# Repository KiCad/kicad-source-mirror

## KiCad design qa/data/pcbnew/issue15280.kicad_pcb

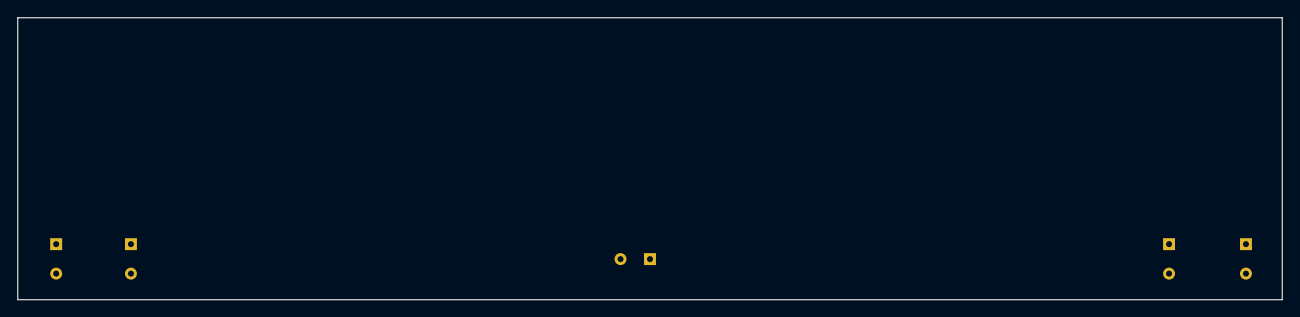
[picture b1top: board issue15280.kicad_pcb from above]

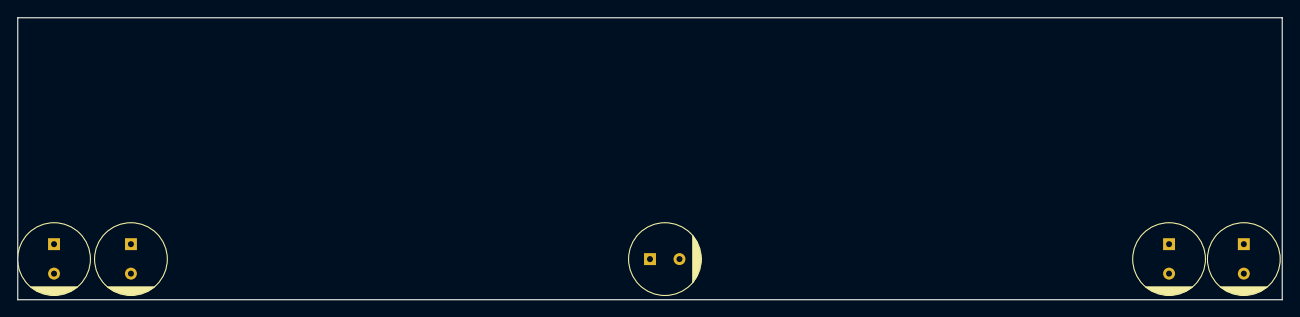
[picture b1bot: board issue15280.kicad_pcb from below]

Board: 8 copper layers, 148.0 x 33.0 mm, 5 parts (5 on the bottom side), 2 nets, no tracks yet.

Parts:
C101, C102, C311, C511, C708: 22u; CP_Rad_D8_H6

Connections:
/Motor1/VMOT: C101.1, C102.1, C311.1, C511.1, C708.1
GND: C101.2, C102.2, C311.2, C511.2, C708.2

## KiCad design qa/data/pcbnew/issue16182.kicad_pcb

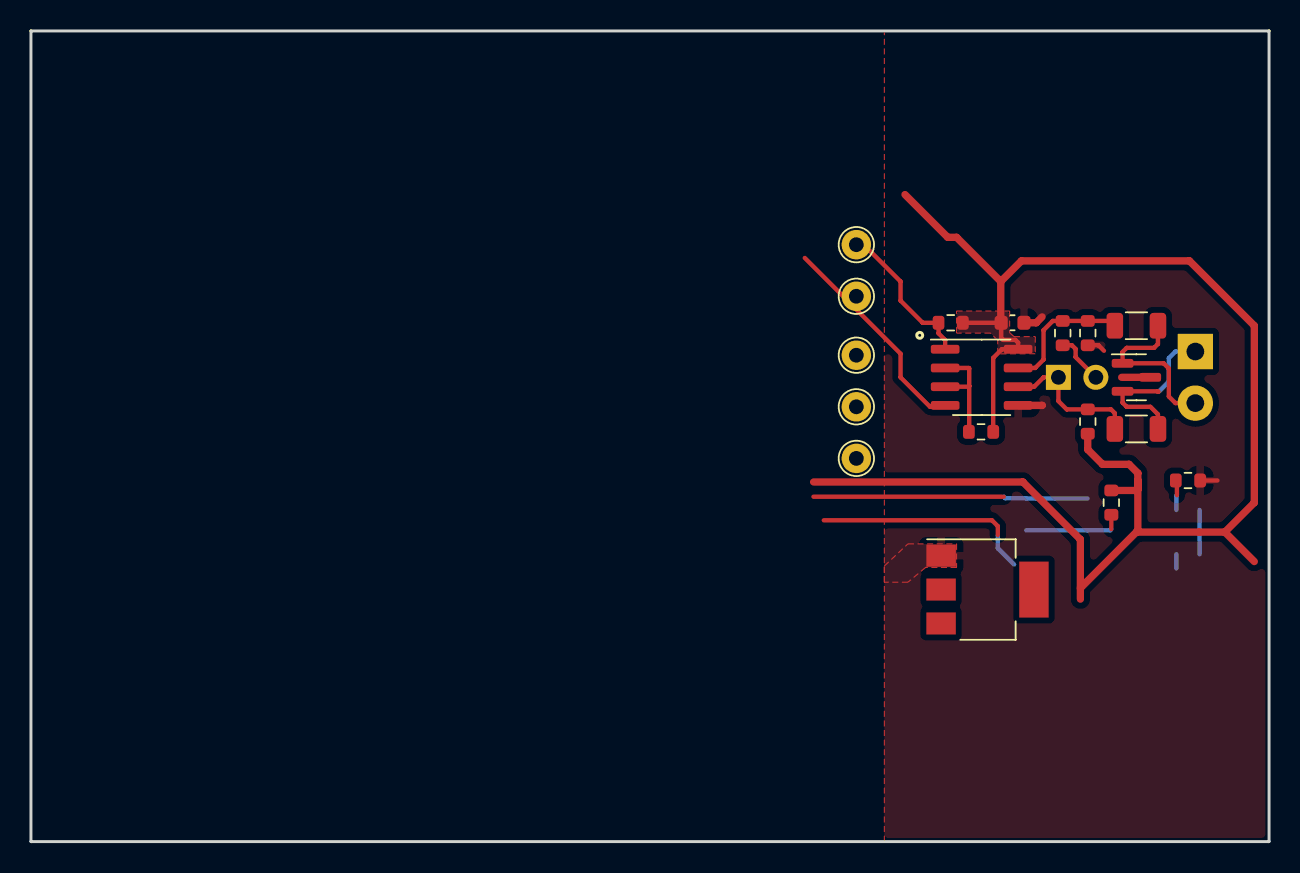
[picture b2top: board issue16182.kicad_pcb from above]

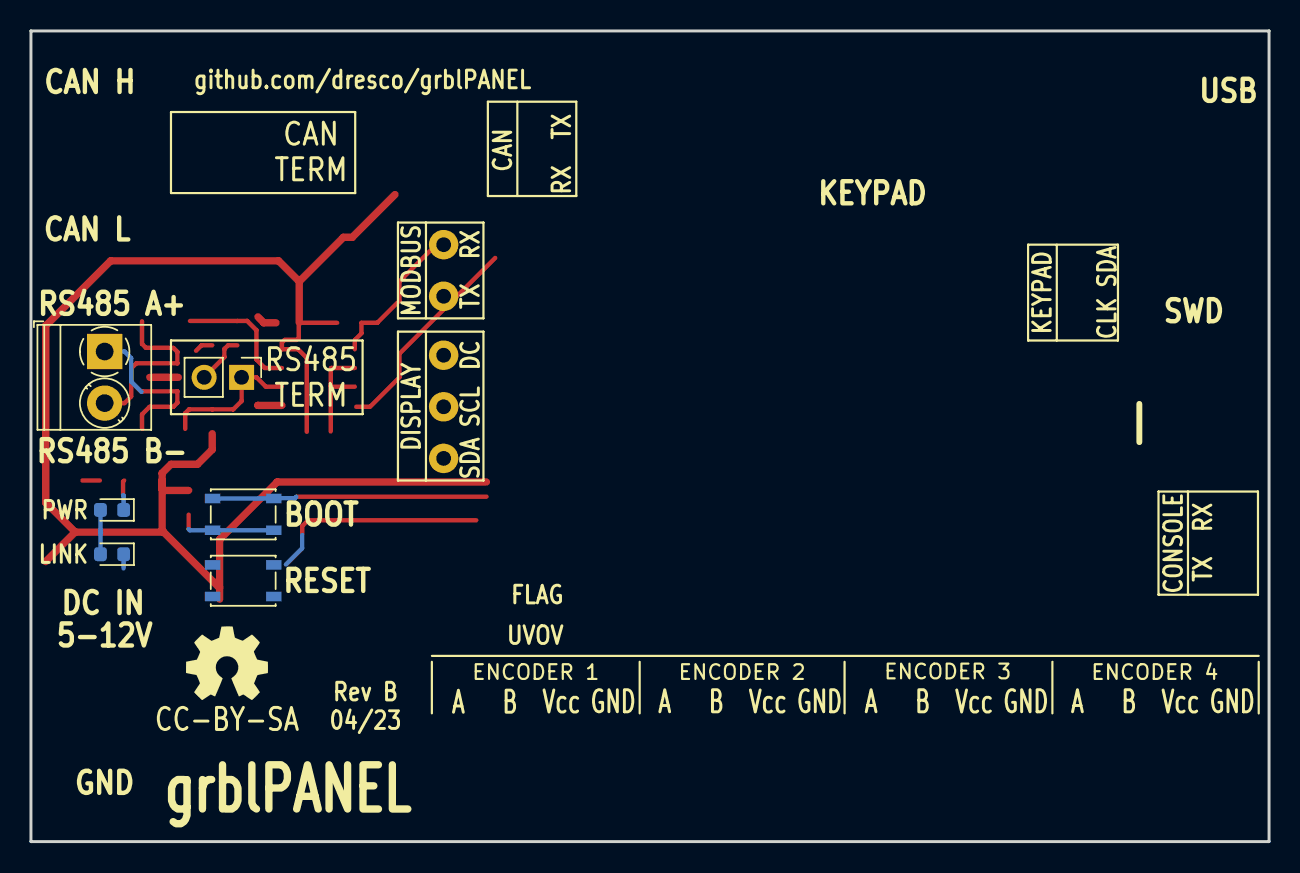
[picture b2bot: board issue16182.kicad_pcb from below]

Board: 4 copper layers, 84.0 x 55.0 mm, 24 parts (6 on the bottom side), 12 nets.

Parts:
C401: 100n; C_0603_1608Metric
D106, D201: LED; LED_0603_1608Metric
D401: CDSOT23-SM712; SOT-23
J401: Conn_01x02; TerminalBlock_Phoenix_PT-1,5-2-3.5-H_1x02_P3.50mm_Horizontal
JP401: Jumper_2_Bridged; PinHeader_1x02_P2.54mm_Vertical
R114: 4k7; R_0603_1608Metric
R202: 200; R_0603_1608Metric
R401, R402: 10k; R_0603_1608Metric
R403: 120; R_0603_1608Metric
R404, R405: DNP; R_0603_1608Metric
R406, R407: 10; R_1206_3216Metric
SW201, SW202: SW_Push; SW_SPST_PTS810
TP401, TP402, TP502, TP503, TP504: TestPoint; TestPoint_THTPad_D2.0mm_Drill1.0mm
U103: AZ1117-3.3; SOT-223-3_TabPin2
U401: THVD1406; SOIC-8_3.9x4.9mm_P1.27mm

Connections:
+3V3: C401.1, D106.2 (A), D201.2 (A), R202.2, R401.1, R402.1, R404.1, U103.2 (VO), U401.8 (Vcc)
/Modbus/CONN_RS485_A: D401.2 (A2), J401.1, R406.2
/Modbus/CONN_RS485_B: D401.1 (A1), J401.2, R407.2
/Modbus/RS485_A: JP401.1 (A), R404.2, R406.1, U401.6 (A)
/Modbus/RS485_B: R403.2, R405.1, R407.1, U401.7 (B)
/Modbus/RS485_MODE_SELECT: R401.2, U401.2 (~RE), U401.3 (~SHDN)
/Power/PWR_LED_K: D106.1 (K), R114.1
GND: C401.2, D401.3 (common), R114.2, R405.2, SW202.2, U103.1 (GND), U401.5 (GND)
MODBUS_RX: R402.2, TP401.1, U401.1 (R)
MODBUS_TX: TP402.1, U401.4 (D)
unnamed: JP401.2 (B), R403.1
unnamed: R202.1, SW201.2

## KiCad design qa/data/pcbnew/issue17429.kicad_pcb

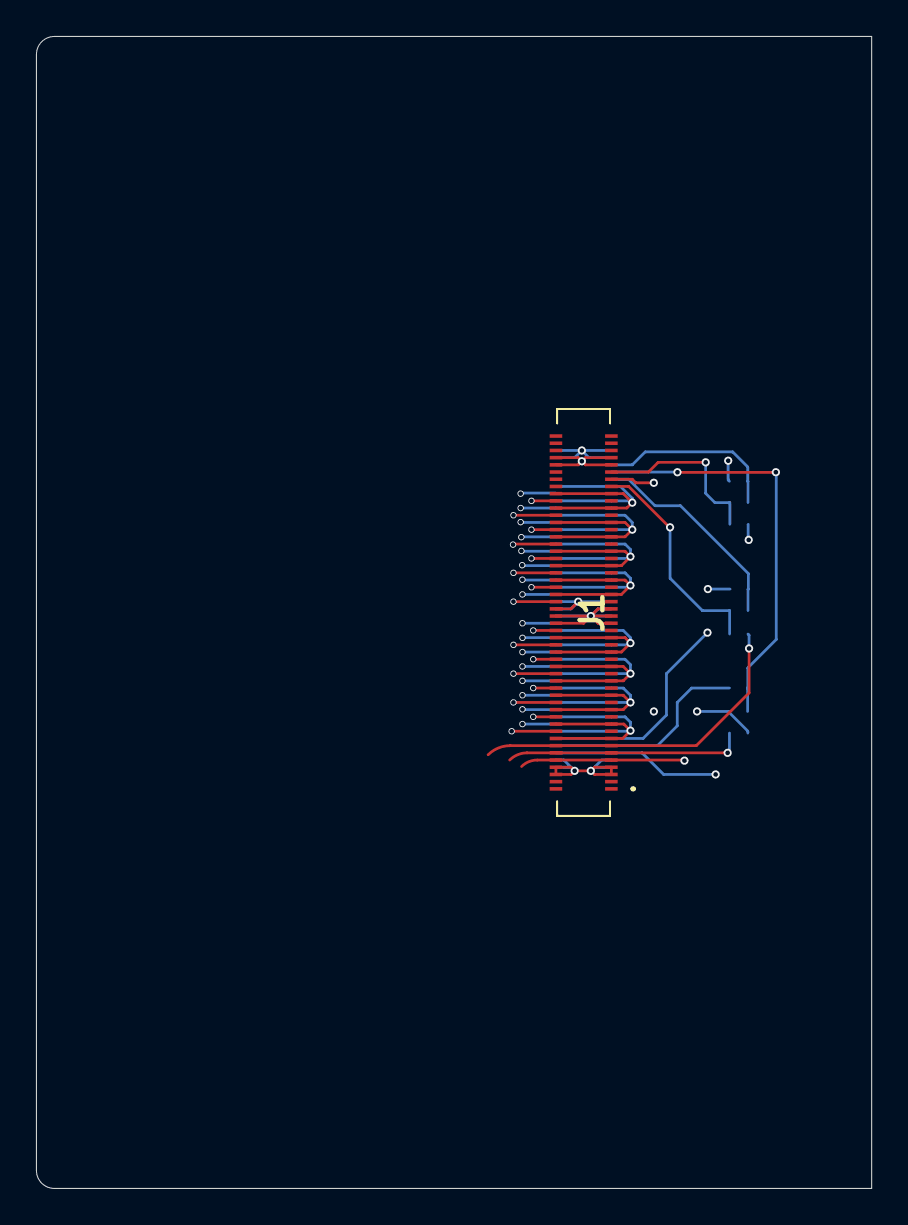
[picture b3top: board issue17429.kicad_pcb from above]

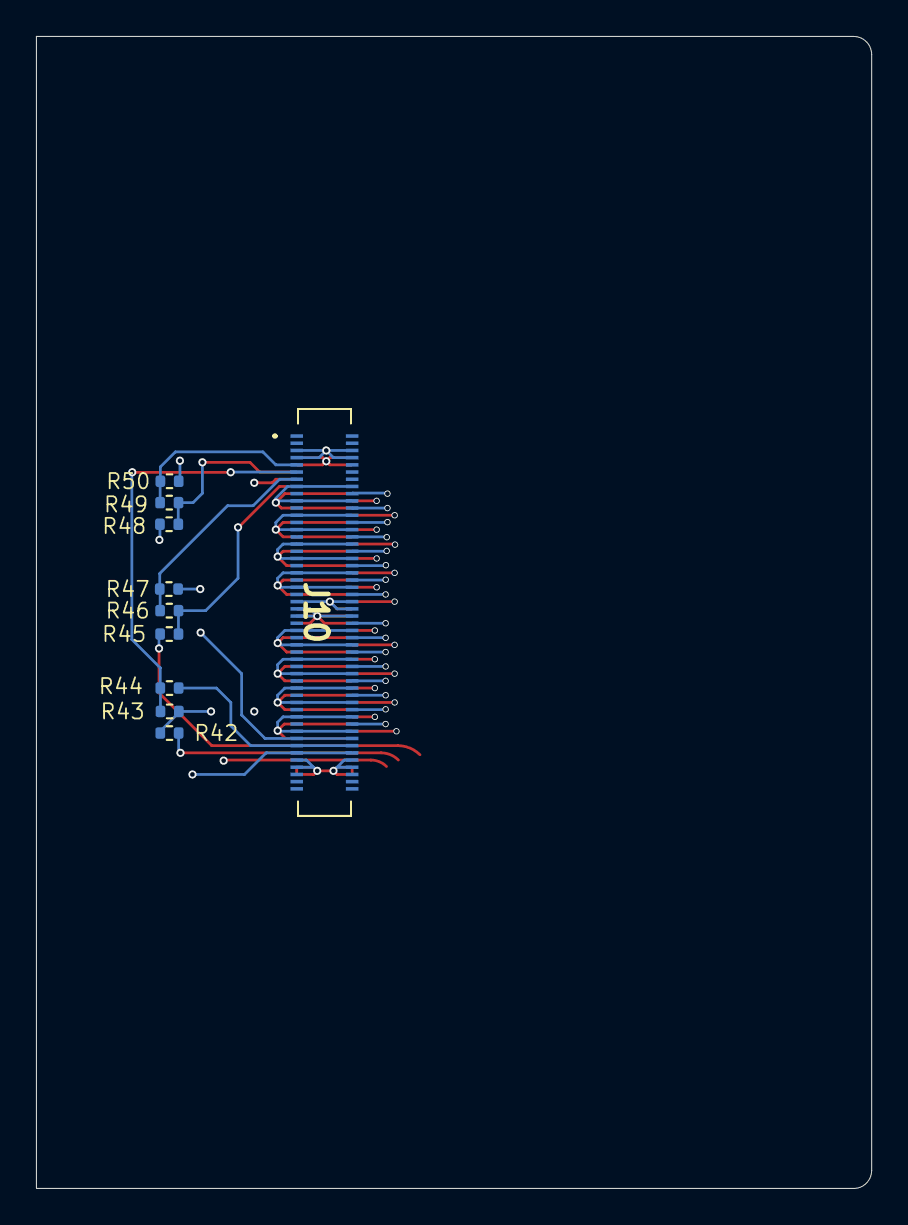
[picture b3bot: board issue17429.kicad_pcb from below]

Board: 8 copper layers, 46.4 x 64.0 mm, 11 parts (10 on the bottom side), 45 nets.

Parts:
J1, J10: DF40HC(3.0)-100DS-0.4V(58); hirose-100-pin-receptacle-DF40HC-3.0-100DS-0.4V-58
R42, R43, R44, R45, R46, R47, R48, R49, R50: 0R; R_0402_1005Metric

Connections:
AGND: J1.5, J1.6, J1.7, J1.8, J1.15, J1.16, J1.19, J1.20, J1.23, J1.24, J1.27, J1.28, J1.31, J1.32, J1.35, J1.36, J1.39, J1.40, J1.43, J1.44, J1.47, J1.48, J1.49, J1.50, J1.51, J1.52, J1.55, J1.56, J1.59, J1.60, J1.63, J1.64, J1.67, J1.68, J1.71, J1.72, J1.75, J1.76, J1.79, J1.80, J1.83, J1.84, J1.91, J1.92, J1.93, J1.94, J10.5, J10.6, J10.7, J10.8, J10.15, J10.16, J10.19, J10.20, J10.23, J10.24, J10.27, J10.28, J10.31, J10.32, J10.35, J10.36, J10.39, J10.40, J10.43, J10.44, J10.47, J10.48, J10.49, J10.50, J10.51, J10.52, J10.55, J10.56, J10.59, J10.60, J10.63, J10.64, J10.67, J10.68, J10.71, J10.72, J10.75, J10.76, J10.79, J10.80, J10.83, J10.84, J10.91, J10.92, J10.93, J10.94
MIM0_ADC0_BIAS_ELEC_CON: J1.11, J1.12, R42.2
MIM0_ADC0_BIAS_REF_CON: J1.9, J1.10, R48.2
MIM0_ADC0_IN1P_CON: J1.17, J1.18
MIM0_ADC0_IN2P_CON: J1.21, J1.22
MIM0_ADC0_IN3P_CON: J1.25, J1.26
MIM0_ADC0_IN4P_CON: J1.29, J1.30
MIM0_ADC0_IN5P_CON: J1.33, J1.34
MIM0_ADC0_IN6P_CON: J1.37, J1.38
MIM0_ADC0_IN7P_CON: J1.41, J1.42
MIM0_ADC0_IN8P_CON: J1.45, J1.46
MIM0_ADC0_REF_ELEC_CON: J1.13, J1.14, R45.2
MIM0_ADC1_BIAS_ELEC_CON: J1.87, J1.88, R42.1, R43.2
MIM0_ADC1_BIAS_REF_CON: J1.89, J1.90, R48.1, R49.2
MIM0_ADC1_IN1P_CON: J1.81, J1.82
MIM0_ADC1_IN2P_CON: J1.77, J1.78
MIM0_ADC1_IN3P_CON: J1.73, J1.74
MIM0_ADC1_IN4P_CON: J1.69, J1.70
MIM0_ADC1_IN5P_CON: J1.65, J1.66
MIM0_ADC1_IN6P_CON: J1.61, J1.62
MIM0_ADC1_IN7P_CON: J1.57, J1.58
MIM0_ADC1_IN8P_CON: J1.53, J1.54
MIM0_ADC1_REF_ELEC_CON: J1.85, J1.86, R45.1, R46.2
MIM1_ADC0_BIAS_ELEC_CON: J10.11, J10.12, R43.1, R44.2
MIM1_ADC0_BIAS_REF_CON: J10.9, J10.10, R49.1, R50.2
MIM1_ADC0_IN1P_CON: J10.17, J10.18
MIM1_ADC0_IN2P_CON: J10.21, J10.22
MIM1_ADC0_IN3P_CON: J10.25, J10.26
MIM1_ADC0_IN4P_CON: J10.29, J10.30
MIM1_ADC0_IN5P_CON: J10.33, J10.34
MIM1_ADC0_IN6P_CON: J10.37, J10.38
MIM1_ADC0_IN7P_CON: J10.41, J10.42
MIM1_ADC0_IN8P_CON: J10.45, J10.46
MIM1_ADC0_REF_ELEC_CON: J10.13, J10.14, R46.1, R47.2
MIM1_ADC1_BIAS_ELEC_CON: J10.87, J10.88, R44.1
MIM1_ADC1_BIAS_REF_CON: J10.89, J10.90, R50.1
MIM1_ADC1_IN1P_CON: J10.81, J10.82
MIM1_ADC1_IN2P_CON: J10.77, J10.78
MIM1_ADC1_IN3P_CON: J10.73, J10.74
MIM1_ADC1_IN4P_CON: J10.69, J10.70
MIM1_ADC1_IN5P_CON: J10.65, J10.66
MIM1_ADC1_IN6P_CON: J10.61, J10.62
MIM1_ADC1_IN7P_CON: J10.57, J10.58
MIM1_ADC1_IN8P_CON: J10.53, J10.54
MIM1_ADC1_REF_ELEC_CON: J10.85, J10.86, R47.1

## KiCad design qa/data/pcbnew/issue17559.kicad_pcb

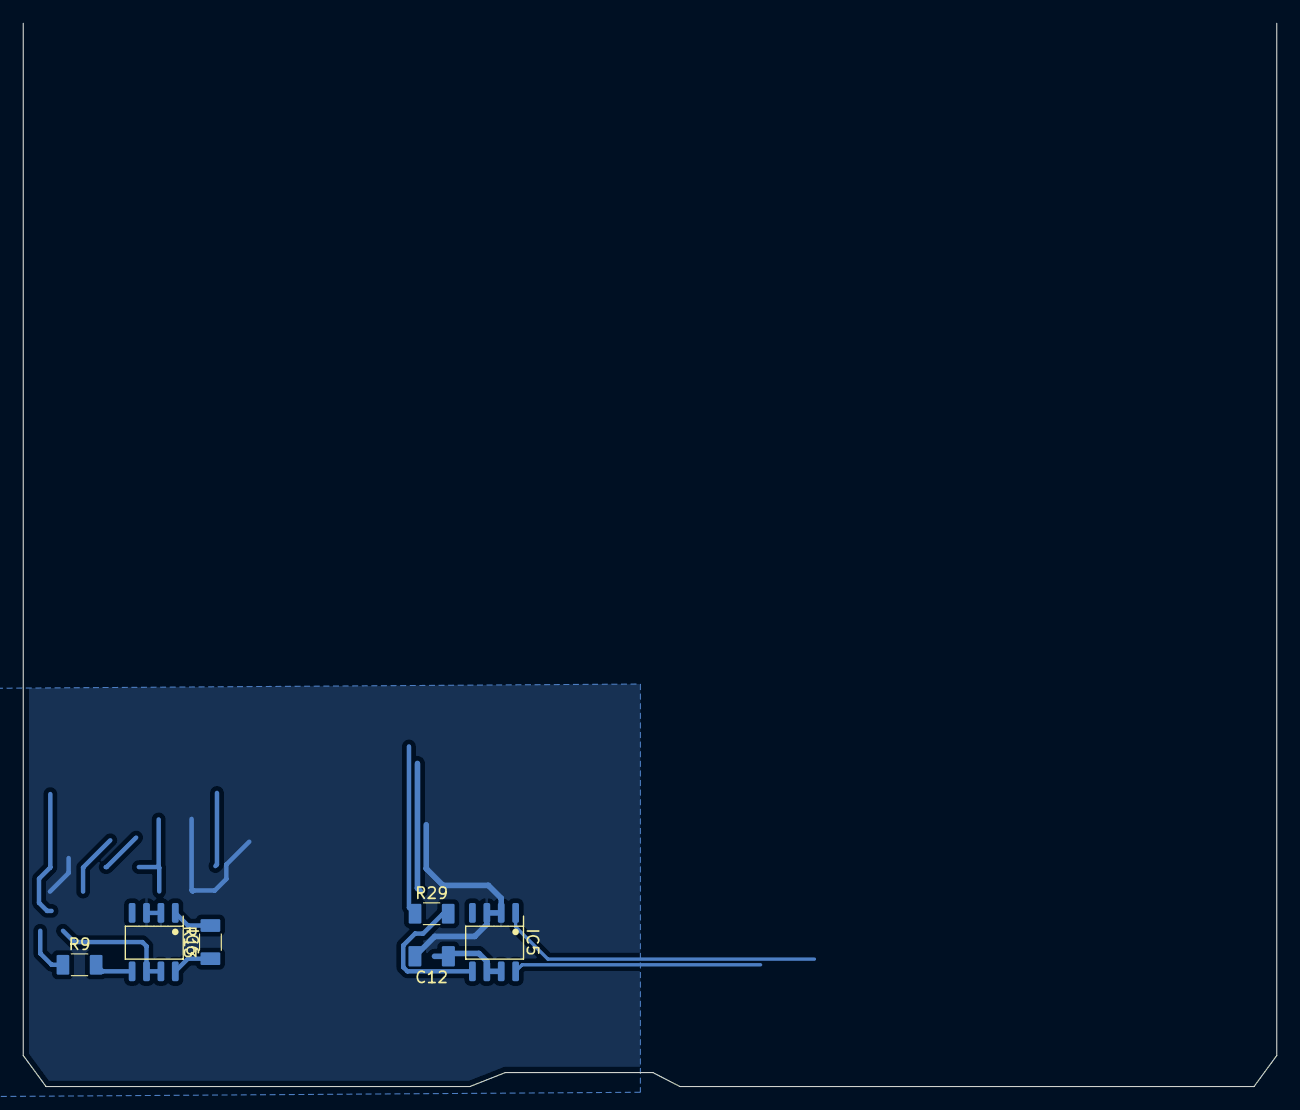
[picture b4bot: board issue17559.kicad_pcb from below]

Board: 2 copper layers, 6 parts (6 on the bottom side), 6 nets.

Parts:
C12: 100nF; C_1206_3216Metric
IC5, IC6: AD8418AWBRZ; SO-8_3.9x4.9mm_P1.27mm_IBF
R9, R13, R29: 1k; R_1206_3216Metric

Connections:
+3V3: C12.1, IC5.6 (vs), IC5.7 (ref1), IC6.6 (vs), IC6.7 (ref1)
GND: C12.2, IC5.2 (gnd), IC5.3 (ref2), IC6.2 (gnd), IC6.3 (ref2)
unnamed: IC5.5 (out), R29.2
unnamed: IC6.8 (+in), R13.1
unnamed: IC6.1 (-in), R13.2
unnamed: IC6.5 (out), R9.2

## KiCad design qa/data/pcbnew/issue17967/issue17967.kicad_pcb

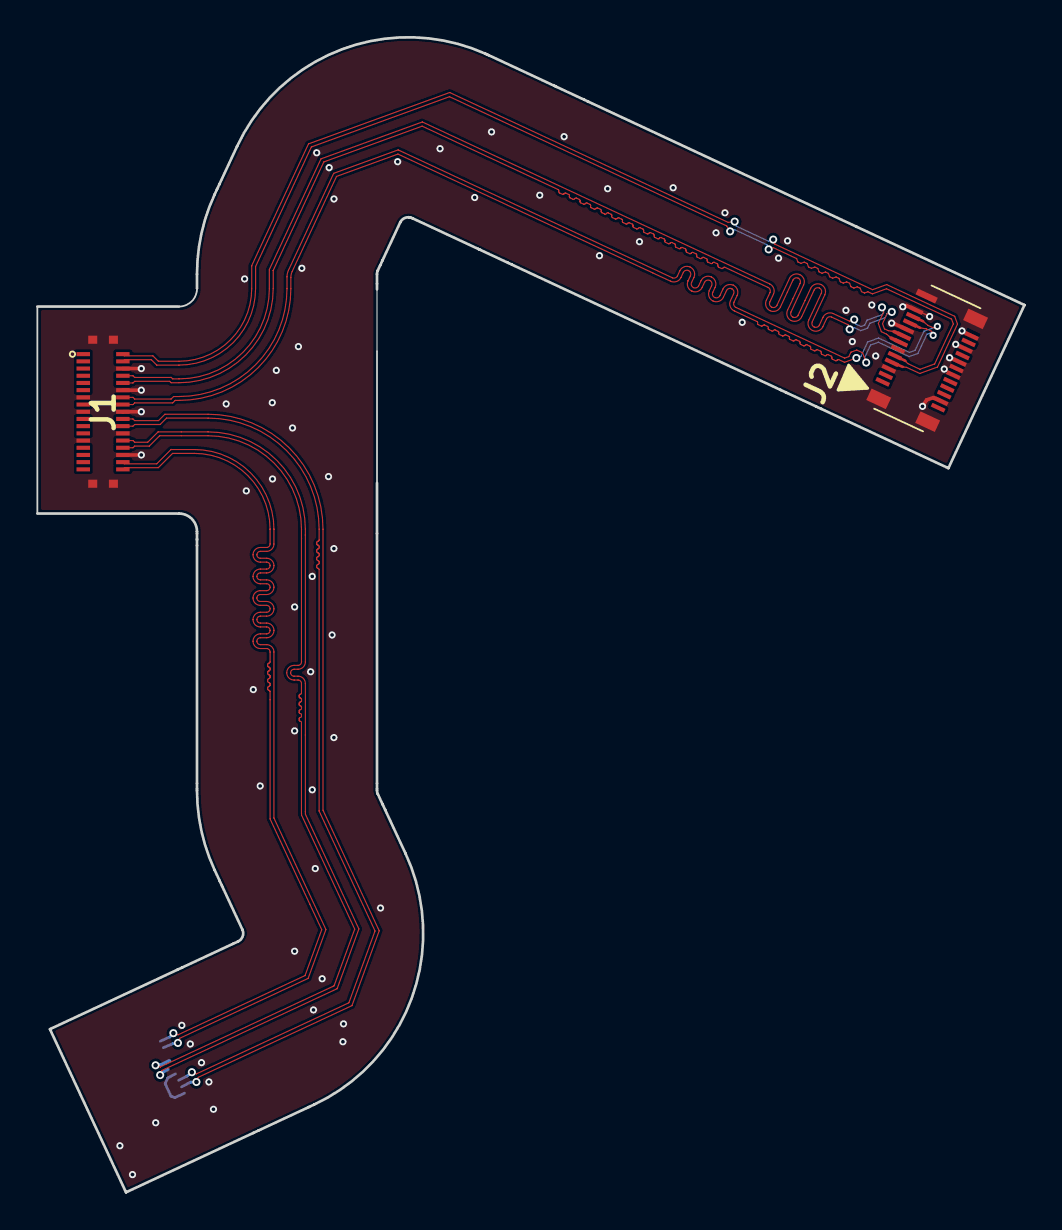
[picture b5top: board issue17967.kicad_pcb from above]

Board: 2 copper layers, 54.8 x 64.2 mm, 3 parts (1 on the bottom side), 13 nets.

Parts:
J1: AXT434124
J2, J3: AXT324124

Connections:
/C_CLK_N: J1.30, J2.5
/C_CLK_P: J1.31, J2.6
/C_D0_N: J1.27, J2.2
/C_D0_P: J1.28, J2.3
/C_D1_N: J1.33, J2.8
/C_D1_P: J1.34, J2.9
/D_CLK_N: J1.21, J3.5
/D_CLK_P: J1.22, J3.6
/D_D0_N: J1.18, J3.2
/D_D0_P: J1.19, J3.3
/D_D1_N: J1.24, J3.8
/D_D1_P: J1.25, J3.9
GND: J1.7, J1.9, J1.13, J1.20, J1.23, J1.26, J1.29, J1.32, J1.MP (MountPin), J2.1, J2.4, J2.7, J2.10, J2.14, J2.18, J2.19, J2.20, J2.22, J2.24, J2.MP (MountPin), J3.1, J3.4, J3.7, J3.10, J3.14, J3.18, J3.19, J3.20, J3.22, J3.24, J3.MP (MountPin)

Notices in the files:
qa/data/pcbnew/issue16182.kicad_pcb:
CC-BY-SA
